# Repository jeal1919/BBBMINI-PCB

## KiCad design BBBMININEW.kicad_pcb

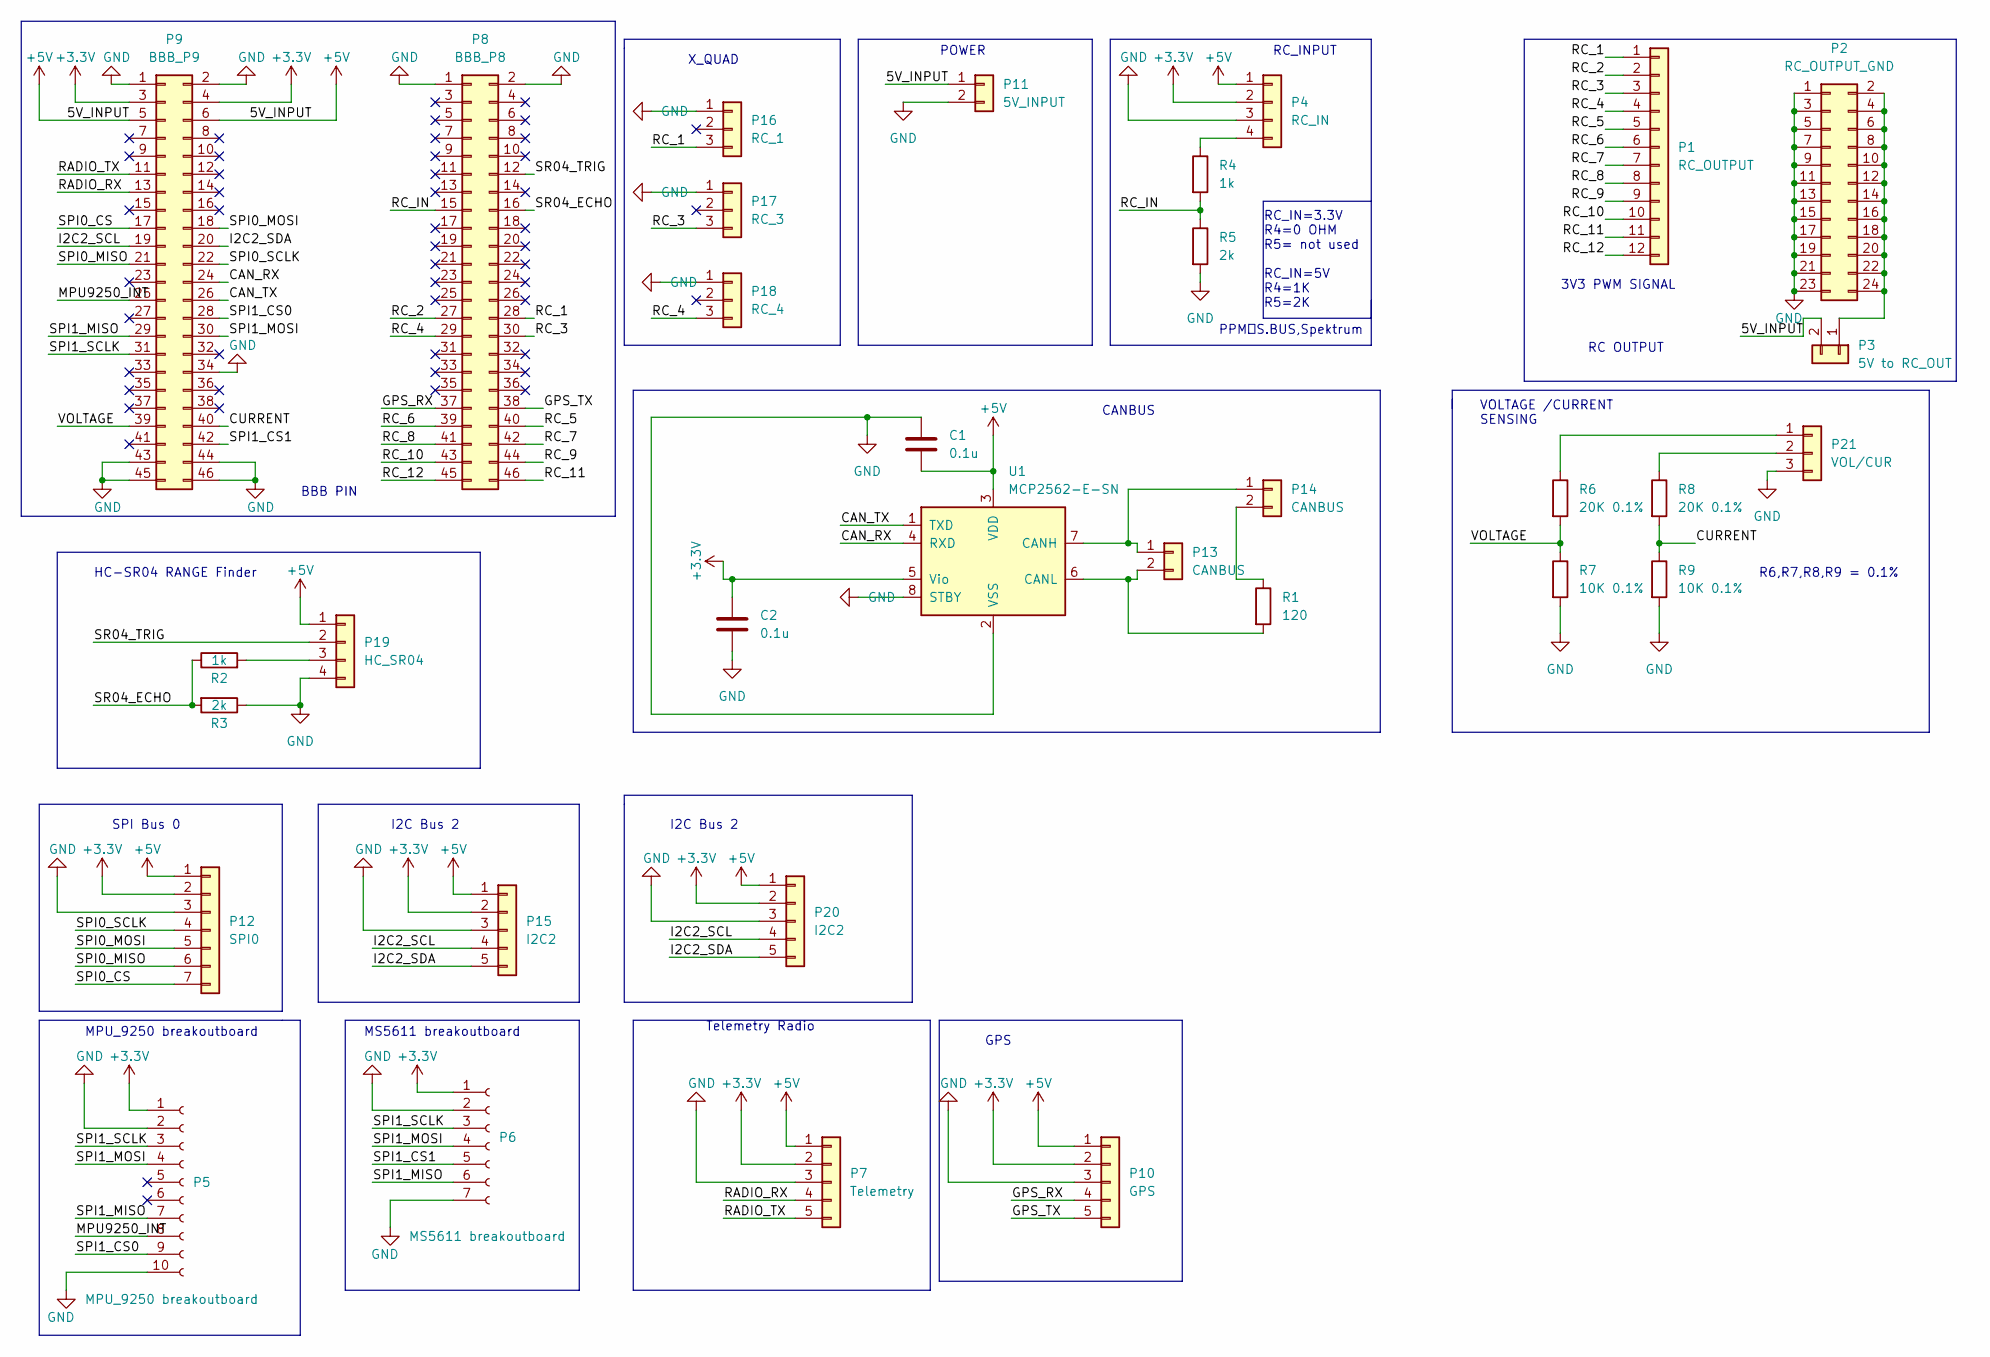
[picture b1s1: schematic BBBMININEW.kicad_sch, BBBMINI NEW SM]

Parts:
C1, C2: 0.1u; C_1210_3225Metric_Pad1.33x2.70mm_HandSolder
P1: RC_OUTPUT; PinHeader_1x12_P2.54mm_Vertical
P2: RC_OUTPUT_GND; PinHeader_2x12_P2.54mm_Vertical
P3: 5V to RC_OUT; PinHeader_1x02_P2.54mm_Vertical
P4: RC_IN; PinHeader_1x04_P2.54mm_Vertical
P5: MPU_9250 breakoutboard; PinSocket_1x10_P2.54mm_Vertical
P6: MS5611 breakoutboard; PinSocket_1x07_P2.54mm_Vertical
P7: Telemetry; PinHeader_1x05_P2.54mm_Vertical
P8: BBB_P8; PinHeader_2x23_P2.54mm_Vertical
P9: BBB_P9; PinHeader_2x23_P2.54mm_Vertical
P10: GPS; PinHeader_1x05_P2.54mm_Vertical
P11: 5V_INPUT; PinHeader_1x02_P2.54mm_Vertical
P12: SPI0; PinHeader_1x07_P2.54mm_Vertical
P13, P14: CANBUS; PinHeader_1x02_P2.54mm_Vertical
P15, P20: I2C2; PinHeader_1x05_P2.54mm_Vertical
P16: RC_1; PinHeader_1x03_P2.54mm_Vertical
P17: RC_3; PinHeader_1x03_P2.54mm_Vertical
P18: RC_4; PinHeader_1x03_P2.54mm_Vertical
P19: HC_SR04; PinHeader_1x04_P2.54mm_Vertical
P21: VOL/CUR; PinHeader_1x03_P2.54mm_Vertical
R1: 120; R_0402_1005Metric_Pad0.72x0.64mm_HandSolder
R2, R4: 1k; R_0805_2012Metric_Pad1.20x1.40mm_HandSolder
R3, R5: 2k; R_2010_5025Metric_Pad1.40x2.65mm_HandSolder
R6, R8: 20K 0.1%; R_0603_1608Metric_Pad0.98x0.95mm_HandSolder
R7, R9: 10K 0.1%; R_0805_2012Metric_Pad1.20x1.40mm_HandSolder
U1: MCP2562-E-SN; SOIC-8_3.9x4.9mm_P1.27mm

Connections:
+3.3V: C2.1, P4.2, P5.1, P6.1, P7.2, P9.3, P9.4, P10.2, P12.2, P15.2, P20.2, U1.5 (Vio)
+5V: C1.2, P3.2, P4.1, P7.1, P9.5, P9.6, P10.1, P11.1, P12.1, P15.1, P19.1, P20.1, U1.3 (VDD)
/CAN_RX: P9.24, U1.4 (RXD)
/CAN_TX: P9.26, U1.1 (TXD)
/CURRENT: P9.40, R8.2, R9.1
/GPS_RX: P8.37, P10.4
/GPS_TX: P8.38, P10.5
/I2C2_SCL: P9.19, P15.4, P20.4
/I2C2_SDA: P9.20, P15.5, P20.5
/MPU9250_INT: P5.8, P9.25
/RADIO_RX: P7.4, P9.13
/RADIO_TX: P7.5, P9.11
/RC_1: P1.1, P8.28, P16.3
/RC_2: P1.2, P8.27
/RC_3: P1.3, P8.30, P17.3
/RC_4: P1.4, P8.29, P18.3
/RC_5: P1.5, P8.40
/RC_6: P1.6, P8.39
/RC_7: P1.7, P8.42
/RC_8: P1.8, P8.41
/RC_9: P1.9, P8.44
/RC_10: P1.10, P8.43
/RC_11: P1.11, P8.46
/RC_12: P1.12, P8.45
/RC_IN: P8.15, R4.2, R5.1
/SPI0_CS: P9.17, P12.7
/SPI0_MISO: P9.21, P12.6
/SPI0_MOSI: P9.18, P12.5
/SPI0_SCLK: P9.22, P12.4
/SPI1_CS0: P5.9, P9.28
/SPI1_CS1: P6.5, P9.42
/SPI1_MISO: P5.7, P6.6, P9.29
/SPI1_MOSI: P5.4, P6.4, P9.30
/SPI1_SCLK: P5.3, P6.3, P9.31
/SR04_ECHO: P8.16, R2.1, R3.2
/SR04_TRIG: P8.12, P19.2
/VOLTAGE: P9.39, R6.2, R7.1
GND: C1.1, C2.2, P2.1, P2.3, P2.5, P2.7, P2.9, P2.11, P2.13, P2.15, P2.17, P2.19, P2.21, P2.23, P4.3, P5.2, P5.10, P6.2, P6.7, P7.3, P8.1, P8.2, P9.1, P9.2, P9.34, P9.43, P9.44, P9.45, P9.46, P10.3, P11.2, P12.3, P15.3, P16.1, P17.1, P18.1, P19.4, P20.3, P21.3, R3.1, R5.2, R7.2, R9.2, U1.2 (VSS), U1.8 (STBY)
unnamed: P2.2, P2.4, P2.6, P2.8, P2.10, P2.12, P2.14, P2.16, P2.18, P2.20, P2.22, P2.24, P3.1
unnamed: P4.4, R4.1
unnamed: P13.1, P14.1, U1.7 (CANH)
unnamed: P13.2, R1.2, U1.6 (CANL)
unnamed: P14.2, R1.1
unnamed: P19.3, R2.2
unnamed: P21.1, R6.1
unnamed: P21.2, R8.1

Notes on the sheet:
I2C Bus 2
Telemetry Radio
X_QUAD
RC_IN=3.3V R4=0 OHM R5= not used RC_IN=5V R4=1K R5=2K
MS5611 breakoutboard
GPS
HC-SR04 RANGE Finder
3V3 PWM SIGNAL
VOLTAGE /CURRENT SENSING
R6,R7,R8,R9 = 0.1%
PPM，S.BUS,Spektrum
CANBUS
BBB PIN
SPI Bus 0
RC_INPUT
MPU_9250 breakoutboard
RC OUTPUT
POWER

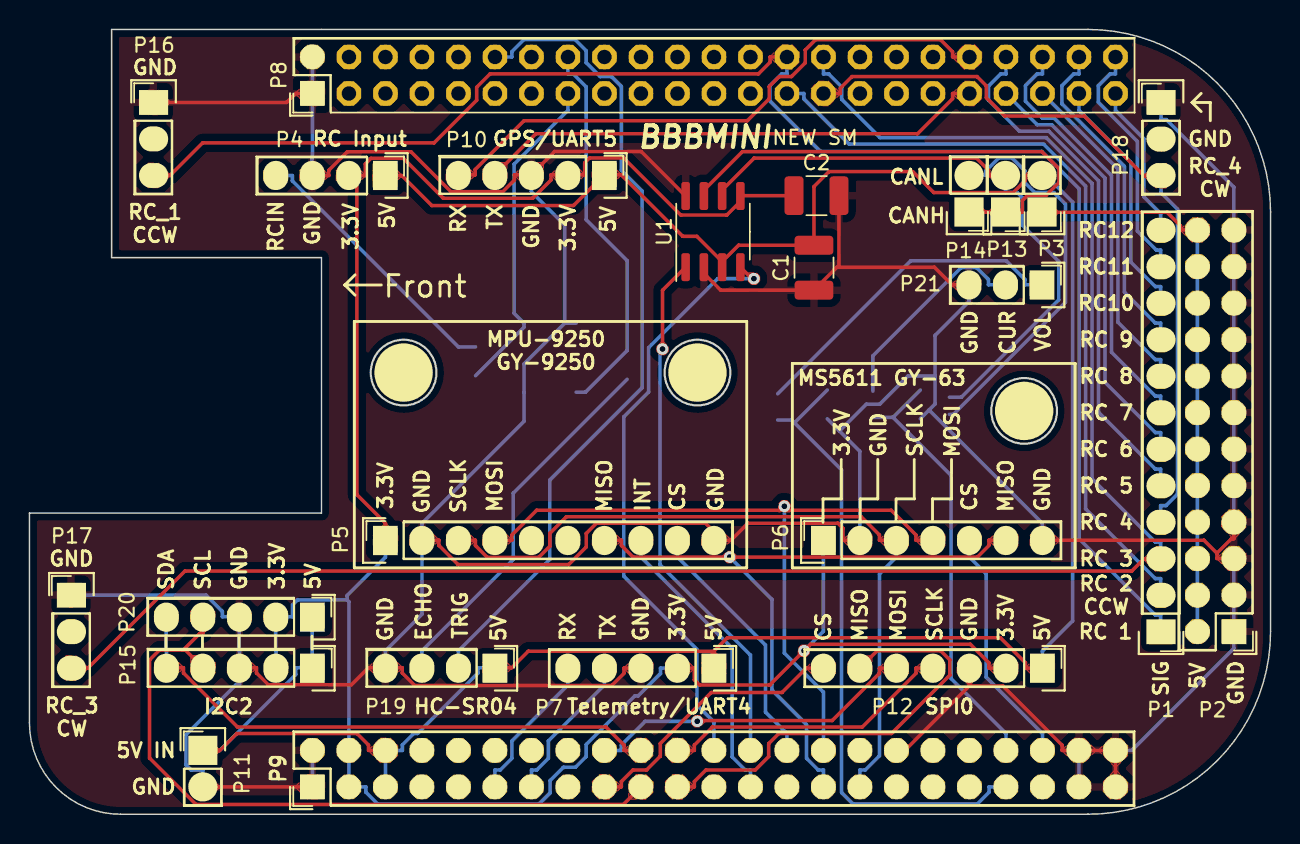
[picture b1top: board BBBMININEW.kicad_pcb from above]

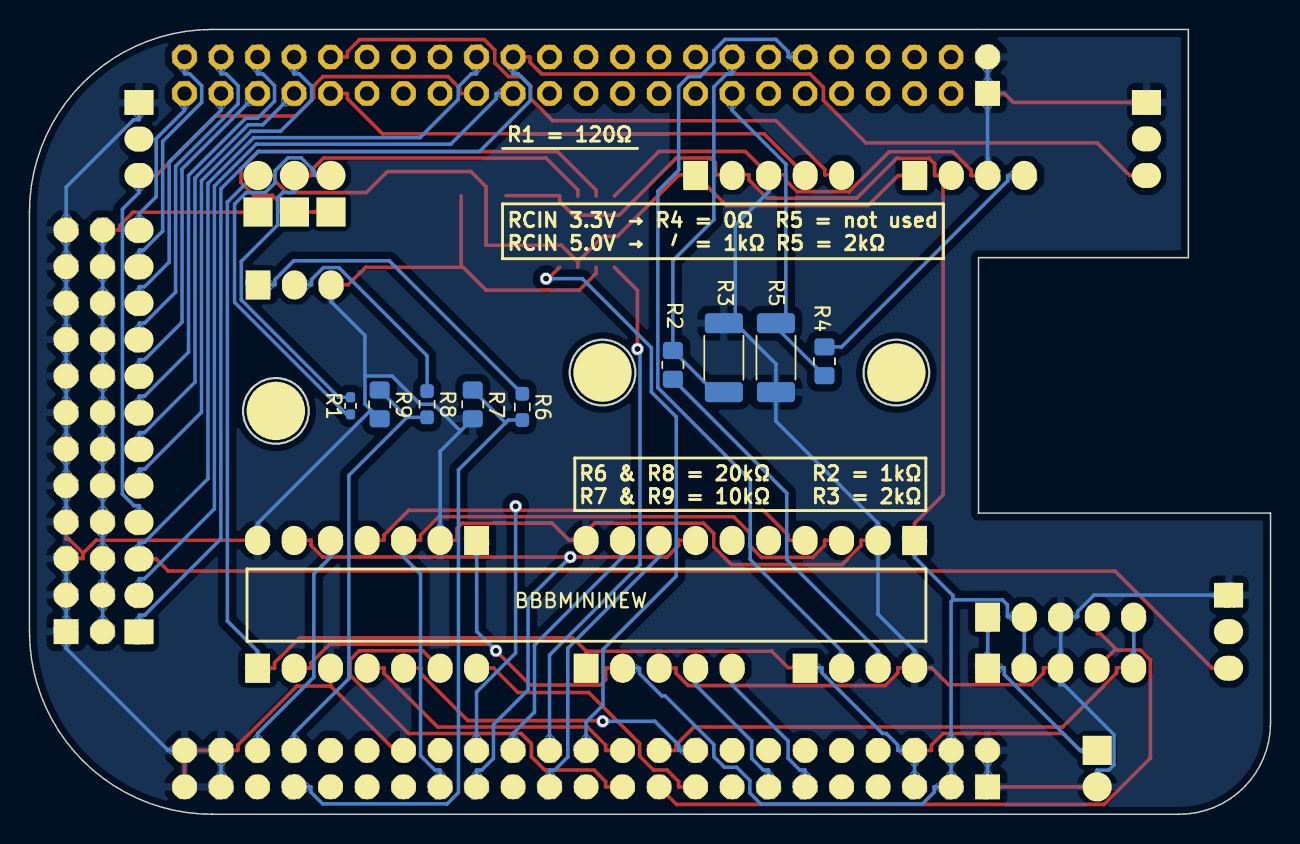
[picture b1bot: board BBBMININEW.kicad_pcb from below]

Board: 2 copper layers, 86.3 x 54.6 mm, 33 parts (9 on the bottom side), 46 nets.

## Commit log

2022-12-17 Add files via upload
    Device DIP component，change to SMT Components and parts
